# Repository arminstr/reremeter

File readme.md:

# reremeter

Reremeter is an handheld and low-cost discrete near infrared reflectance spectrometer and a machine learning algorithm developed to detect different types of plastic. Watch our [video](https://www.youtube.com/watch?v=hrVgNUm2_Jo) to find out more!

This repository contains all the files required to build an reremeter from scratch, and you can use them to make your own version. Please take note that this work is published under GPL-3.0. 

### How to get started
> Please note the current *Issues* before getting started with the build of your own reremeter.

Now the guide on how to get started with the build of your own reremeter.
- Build your own [hardware](./hardware).
- Build and upload the [firmware](./firmware).
- Collect data of your samples (or check out our example [dataset](./data)).
- Make Predictions using our provided Python [scripts](./software).
- Visualize results in an [UI](./webapp).

### Additional information 
- The main idea behind this project came from reading this paper about [Identification and classification of plastic resins using near infrared reflectance spectroscopy](https://www.researchgate.net/publication/285330830_Identification_and_classification_of_plastic_resins_using_near_infrared_reflectance_spectroscopy) by Hamed Masoumi, Seyed Mohsen Safavi, and Zahra Khani.
- Inspiration for the analog frontend design was given by the [ADS1255](https://www.ti.com/product/ADS1255) reference designs on the TI website. They used this ADC in several DLP NIR spectrometer designs. (e.g. [DLP® NIRscan™ Evaluation Module](https://www.ti.com/tool/DLPNIRSCANEVM#2), [DLP Ultra-mobile NIR Spectrometer for Portable Chemical Analysis with Bluetooth Connectivity](https://www.ti.com/tool/TIDA-00554))
- Super interesting [MEMS spectrum sensor](https://www.hamamatsu.com/eu/en/product/type/C13272-02/index.html). You can read more about this on [OpenRecycling](https://openrecycling.com/en/projects/2021/01/06/plastic-type-sensor.html). 

### Notes
The reremeter project was created at RealRecycling by Armin Straller and Bernhard Gessler.

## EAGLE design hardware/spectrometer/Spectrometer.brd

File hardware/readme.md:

# hardware v2

We are currently working on a second version of the low cost plastic sensor based on a MEMS-FPI chip by HAMAMATSU.

This folder now contains the schematics in the folders spectrometer-2 and usb-interface-2.

# reremeter hardware

This folder contains all of the source files for making your own reremeter PCB hardware: a Autodesk Eagle project file for the PCB in spectrometer/, rendered gerber files from the Eagle project in manufacturing/, and exported schematics in this [file](Spectrometer_Schematic.pdf).

The PCB design includes mainly SMT components as the handheld form factor was design criteria. It is possible to assemble individual boards by hand in a few hours (if you bring in decent SMT soldering skills), however for multiple boards it would be advisable to order multiple fully assembled (or at least SMT assembled) PCBs. If you wish to have the PCB manufactured, the files in manufacturing/ should be all you need; additionally, a bill of materials is available [here](manufacturing/Spectrometer_BOM.txt).

Following parts on the BOM previously raised issues:
- X301 is a quartz crystal with 8MHz: FL0800008QDICT-ND
- X302 is a 9pin ARM debug connector: SAM9438-ND
- D20 is a 800nm ~ 1700nm photodetector: 209-003-151-001CT-ND

The mentioned part numbers are from DigiKey. The 8MHz quartz is a replacement part that should fit properly.

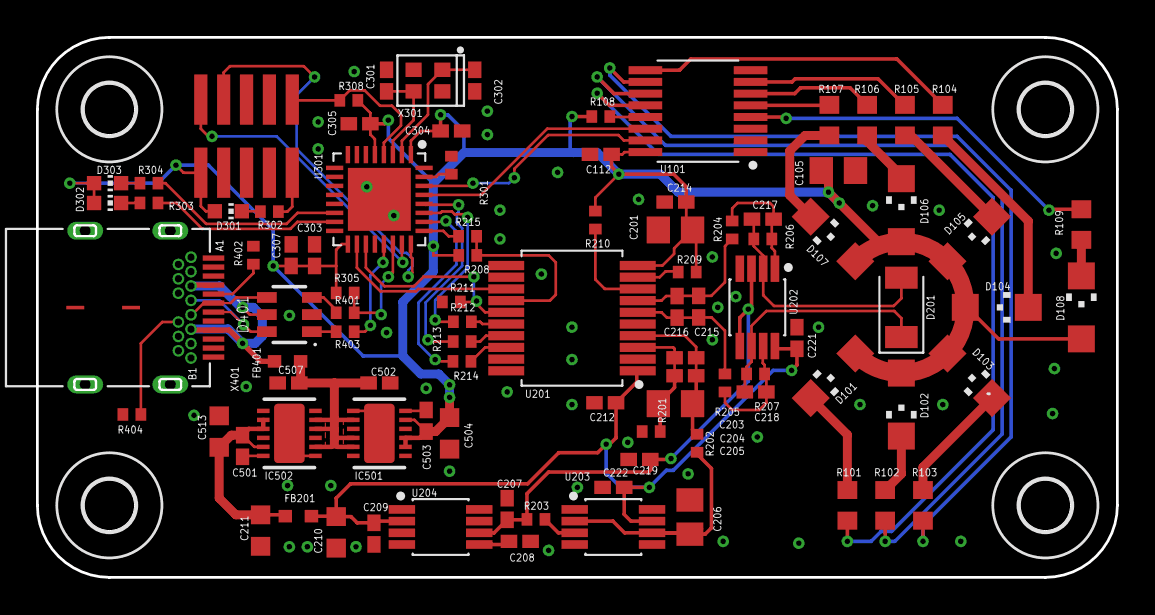
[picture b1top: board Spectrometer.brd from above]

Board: 2 copper layers, 60.0 x 30.0 mm, 97 parts (0 on the bottom side), 69 nets.

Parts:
C105, C205, C206: 22uF; C0805
C112, C204, C212, C214, C219, C221, C222, C303, C304, C305: 100nF; C0402K
C201: 10uF; C0805
C203, C216: 100pF; C0402K
C207, C208, C209, C307, C502, C507: 1uF; C0402K
C210, C211: 15uF; C0603K
C215: 47nF; C0402K
C217, C218: 51pF; C0402K
C301, C302: 10pF; C0402K
C501, C503: 10nF; C0402K
C504, C513: 10uF; C0603K
D101: 1650nm; CHIPLED_1206
D102: 1550nm; CHIPLED_1206
D103: 1450nm; CHIPLED_1206
D104: 1300nm; CHIPLED_1206
D105: 1200nm; CHIPLED_1206
D106: 940nm; CHIPLED_1206
D107: 850nm; CHIPLED_1206
D108: white; CHIPLED_1206
D201: SD003-151-001SMD; LEDC3316X110
D301, D303: green; CHIP-LED0603
D302: orange; CHIP-LED0603
D401: 5Vdc; WE-TVS_SOT23-6L
FB201, FB401: 240Ohm@100MHz; WE-CBF_0603(W=2.2)
H1, H2, H3, H4: MOUNT-HOLE2.8; 2,8
IC501: LT1763IDE-3.3; DFN12
IC502: LT1763IDE-5; DFN12
R101, R102, R103, R104, R105: 43; R0603
R106: 39; R0603
R107: 36; R0603
R108, R208, R209, R210, R211, R308: 100k; R0402
R109: 6.8; R0603
R201, R202: 49.9; R0402
R203, R301: 10k; R0402
R204, R205: 301; R0402
R206, R207: 240k; R0402
R212, R213, R214, R215: 100; R0402
R302, R303, R304: 1k; R0402
R305: 1k5; R0402
R401, R403: 22R; R0402
R402, R404: 5k1; R0402
U101: TLC59208FTSSOP-16; SOP65P640X120-16
U201: ADS1255TSSOP; SOP65P780X200-20
U202: OPA2376PDSO-8; SOP65P490X110-8
U203: OPA350PDSO-8; SOP65P490X110-8
U204: REF5025PDSO-8; SOP65P490X110-8
U301: STM32F302K8U6UFQFPN32; QFN50P500X500X60-33T350
X301: 8MHz; 2.6X2.1-4-PAD
X302: CORTEX-MDEBUG-10P; CORTEX-M-CON-10P
X401: 632723300011THT; USBC_HORZONTAL_WE

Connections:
+3V3: C105.2, C112.1, C201.2, C214.1, C303.1, C304.1, C305.1, C307.1, C503.2, C504.2, D101.A, D102.A, D103.A, D104.A, D105.A, D106.A, D107.A, D108.A, D301.A, D302.A, D303.A, IC501.2, IC501.3, IC501.5, R108.1, R208.2, R209.2, R210.2, R305.1, R308.1, U101.16, U201.10, U301.1, U301.5, U301.17, X302.P$1
+5V: C211.2, C501.2, C513.2, FB201.1, IC502.2, IC502.3, IC502.5
ADC1:2V5REF: C207.1, C219.1, R203.2, U202.3, U202.5, U204.6
ADC1:2V5REFBUF: C206.2, R202.2, U203.2, U203.6
ADC1:5V0F: C209.1, C210.2, C212.1, C221.1, C222.1, FB201.2, U201.1, U202.8, U203.7, U204.2
ADC1:ANODE: C217.1, D201.2, R206.2, U202.2
ADC1:CATHODE: C218.1, D201.1, R207.2, U202.6
ADC1:CSZ: R208.1, R215.2, U201.14
ADC1:DIN: R213.2, U201.17
ADC1:DOUT: R212.2, U201.16
ADC1:N$3: C203.2, C204.2, C205.2, R201.2, U201.3
ADC1:N$4: C203.1, C204.1, C205.1, R202.1, U201.4
ADC1:N$5: R203.1, U203.3
ADC1:N$6: C208.1, U204.5
ADC1:N$7: C217.2, R204.2, R206.1, U202.1
ADC1:N$8: C218.2, R205.2, R207.1, U202.7
ADC1:N$9: C215.2, C216.2, R205.1, U201.6
ADC1:N$10: C215.1, C216.1, R204.1, U201.7
ADC1:N$11: R209.1, U201.9
ADC1:SCLK: R214.2, U201.18
ADC1:SYNCZ: R210.1, U201.8
D+: R305.2, R401.1, U301.22
D-: R403.1, U301.21
DRDYZ: R211.2, U201.15, U301.19
GND: C105.1, C112.2, C201.1, C206.1, C207.2, C208.2, C209.2, C210.1, C211.1, C212.2, C214.2, C219.2, C221.2, C222.2, C301.2, C302.2, C303.2, C304.2, C305.2, C307.2, C502.2, C504.1, C507.2, C513.1, D401.2, IC501.7, IC501.EXP, IC502.7, IC502.EXP, R201.1, R211.1, R301.1, R402.2, R404.2, U101.1, U101.2, U101.3, U101.8, U201.2, U201.5, U201.11, U201.20, U202.4, U203.4, U204.4, U301.6, U301.16, U301.32, U301.33, X301.2, X301.4, X302.P$3, X302.P$5, X401.A1, X401.A12, X401.B1, X401.B12, X401.GND, X401.GND1, X401.Z1, X401.Z2, X401.Z3, X401.Z4, X401.Z5, X401.Z6
LED1:N$1: R101.1, U101.12
LED1:N$2: R102.1, U101.11
LED1:N$3: R103.1, U101.10
LED1:N$4: R104.1, U101.9
LED1:N$5: R105.1, U101.7
LED1:N$6: R106.1, U101.6
LED1:N$7: R107.1, U101.5
LED1:N$8: R109.1, U101.4
LED1:N$9: D108.C, R109.2
LED1:N$10: D107.C, R107.2
LED1:N$11: D106.C, R106.2
LED1:N$12: D105.C, R105.2
LED1:N$13: D104.C, R104.2
LED1:N$14: D103.C, R103.2
LED1:N$15: D102.C, R102.2
LED1:N$16: D101.C, R101.2
LED1:NRST: R108.2, U101.13
MCO: U201.13, U301.18
MCU1:HSE_IN: C302.1, U301.2, X301.1
MCU1:HSE_OUT: C301.1, U301.3, X301.3
MCU1:N$1: R304.1, U301.14
MCU1:N$2: R301.2, U301.31
MCU1:N$3: R302.1, X302.P$9
MCU1:N$4: D301.C, R302.2
MCU1:N$5: R303.1, U301.15
MCU1:N$6: D303.C, R304.2
MCU1:N$7: D302.C, R303.2
MCU1:NRST: R308.2, U301.4, X302.P$10
MCU1:SWCLK: U301.24, X302.P$4
MCU1:SWDIO: U301.23, X302.P$2
MISO: R212.1, U301.27
MOSI: R213.1, U301.28
NSS: R215.1, U301.25
SCK: R214.1, U301.26
SCL: U101.14, U301.29
SDA: U101.15, U301.30
SUPPLY5:N$1: C501.1, IC502.6
SUPPLY5:N$2: C503.1, IC501.6
USB1:CC1: R402.1, X401.A5
USB1:CC2: R404.1, X401.B5
USB1:DN: D401.1, D401.6, R403.2, X401.A7, X401.B7
USB1:DP: D401.3, D401.4, R401.2, X401.A6, X401.B6
USB1:VBUS: D401.5, FB401.1, X401.A4, X401.A9, X401.B4, X401.B9
V+: C502.1, C507.1, FB401.2, IC501.8, IC501.10, IC501.11, IC502.8, IC502.10, IC502.11

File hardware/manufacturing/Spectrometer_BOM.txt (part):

Partlist exported from /Users/armin/CloudStation/02_projects/18_realrecycling/02_dev/01_sensor/02_hardware/pcb/spectrometer/Spectrometer.sch at 07.12.19 15:55

Qty Value                 Device                      Package                 Parts                                                      Description                                 MF MPN               OC_FARNELL OC_NEWARK SPICEPREFIX VALUE    WE-NUMBER               
4   100                   R-EU_R0402                  R0402                   R212, R213, R214, R215                                     RESISTOR, European symbol                                                             R                                            
6   100k                  R-EU_R0402                  R0402                   R108, R208, R209, R210, R211, R308                         RESISTOR, European symbol                                                             R                                            
10  100nF                 C-EUC0402K                  C0402K                  C112, C204, C212, C214, C219, C221, C222, C303, C304, C305 CAPACITOR, European symbol                                                            C                                            
2   100pF                 C-EUC0402K                  C0402K                  C203, C216                                                 CAPACITOR, European symbol                                                            C                                            
2   10k                   R-EU_R0402                  R0402                   R203, R301                                                 RESISTOR, European symbol                                                             R                                            
2   10nF                  C-EUC0402K                  C0402K                  C501, C503                                                 CAPACITOR, European symbol                                                            C                                            
2   10pF                  C-EUC0402K                  C0402K                  C301, C302                                                 CAPACITOR, European symbol                                                            C                                            
2   10uF                  C-EUC0603K                  C0603K                  C504, C513                                                 CAPACITOR, European symbol                                                            C                                            
1   10uF                  C-EUC0805                   C0805                   C201                                                       CAPACITOR, European symbol                                                            C                                            
1   1200nm                LEDCHIPLED_1206             CHIPLED_1206            D105                                                       LED                                                                                                                                
1   1300nm                LEDCHIPLED_1206             CHIPLED_1206            D104                                                       LED                                                                                                                                
1   1450nm                LEDCHIPLED_1206             CHIPLED_1206            D103                                                       LED                                                                                                                                
1   1550nm                LEDCHIPLED_1206             CHIPLED_1206            D102                                                       LED                                                                                                                                
2   15uF                  C-EUC0603K                  C0603K                  C210, C211                                                 CAPACITOR, European symbol                                                            C                                            
1   1650nm                LEDCHIPLED_1206             CHIPLED_1206            D101                                                       LED                                                                                                                                
3   1k                    R-EU_R0402                  R0402                   R302, R303, R304                                           RESISTOR, European symbol                                                             R                                            
1   1k5                   R-EU_R0402                  R0402                   R305                                                       RESISTOR, European symbol                                                             R                                            
6   1uF                   C-EUC0402K                  C0402K                  C207, C208, C209, C307, C502, C507                         CAPACITOR, European symbol                                                            C                                            
2   22R                   R-EU_R0402                  R0402                   R401, R403                                                 RESISTOR, European symbol                                                             R                                            
3   22uF                  C-EUC0805                   C0805                   C105, C205, C206                                           CAPACITOR, European symbol                                                            C                                            
2   240                   WE-CBF_0603_742792631_WB_HS WE-CBF_0603(W=2.2)      FB201, FB401                                               WE-CBF SMD EMI Suppression Ferrite Bead                                                                    742792631/240Ω(Z@100MHz)
2   240k                  R-EU_R0402                  R0402                   R206, R207                                                 RESISTOR, European symbol                                                             R                                            
2   301                   R-EU_R0402                  R0402                   R204, R205                                                 RESISTOR, European symbol                                                             R                                            
1   36                    R-EU_R0603                  R0603                   R107                                                       RESISTOR, European symbol                                                             R                                            
1   39                    R-EU_R0603                  R0603                   R106                                                       RESISTOR, European symbol                                                             R                                            
5   43                    R-EU_R0603                  R0603                   R101, R102, R103, R104, R105                               RESISTOR, European symbol                                                             R                                            
1   47nF                  C-EUC0402K                  C0402K                  C215                                                       CAPACITOR, European symbol                                                            C                                            
2   49.9                  R-EU_R0402                  R0402                   R201, R202                                                 RESISTOR, European symbol                                                             R                                            
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
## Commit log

2019-12-09 Changed Firmware README
2019-12-09 Edited further readme.md descriptions
2019-12-09 Updated hardware readme.md
2019-12-09 Edited case and webapp readme.md
2019-12-09 edited software readme.md
2019-12-09 edited software readme
2019-12-09 edited readme.md
2019-12-09 Edited webapp readme.md
2019-12-13 Added note about Issues to readme.md
2020-08-22 typo
2020-09-02 Update readme.md
    clarified BOM issues
2020-09-02 changed library dependencies
2020-11-13 added schematics for second version of the sensor
2020-11-13 added LT spice simulation for MEMS-FPI voltage
2020-11-24 Added mechanical and interface details of V2
2021-11-26 Added link to OpenRecycling and HAMAMATSU

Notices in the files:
parts and their libraries:
Wurth_EMC Components_WE-CBF: Copyright: Würth Elektronik
